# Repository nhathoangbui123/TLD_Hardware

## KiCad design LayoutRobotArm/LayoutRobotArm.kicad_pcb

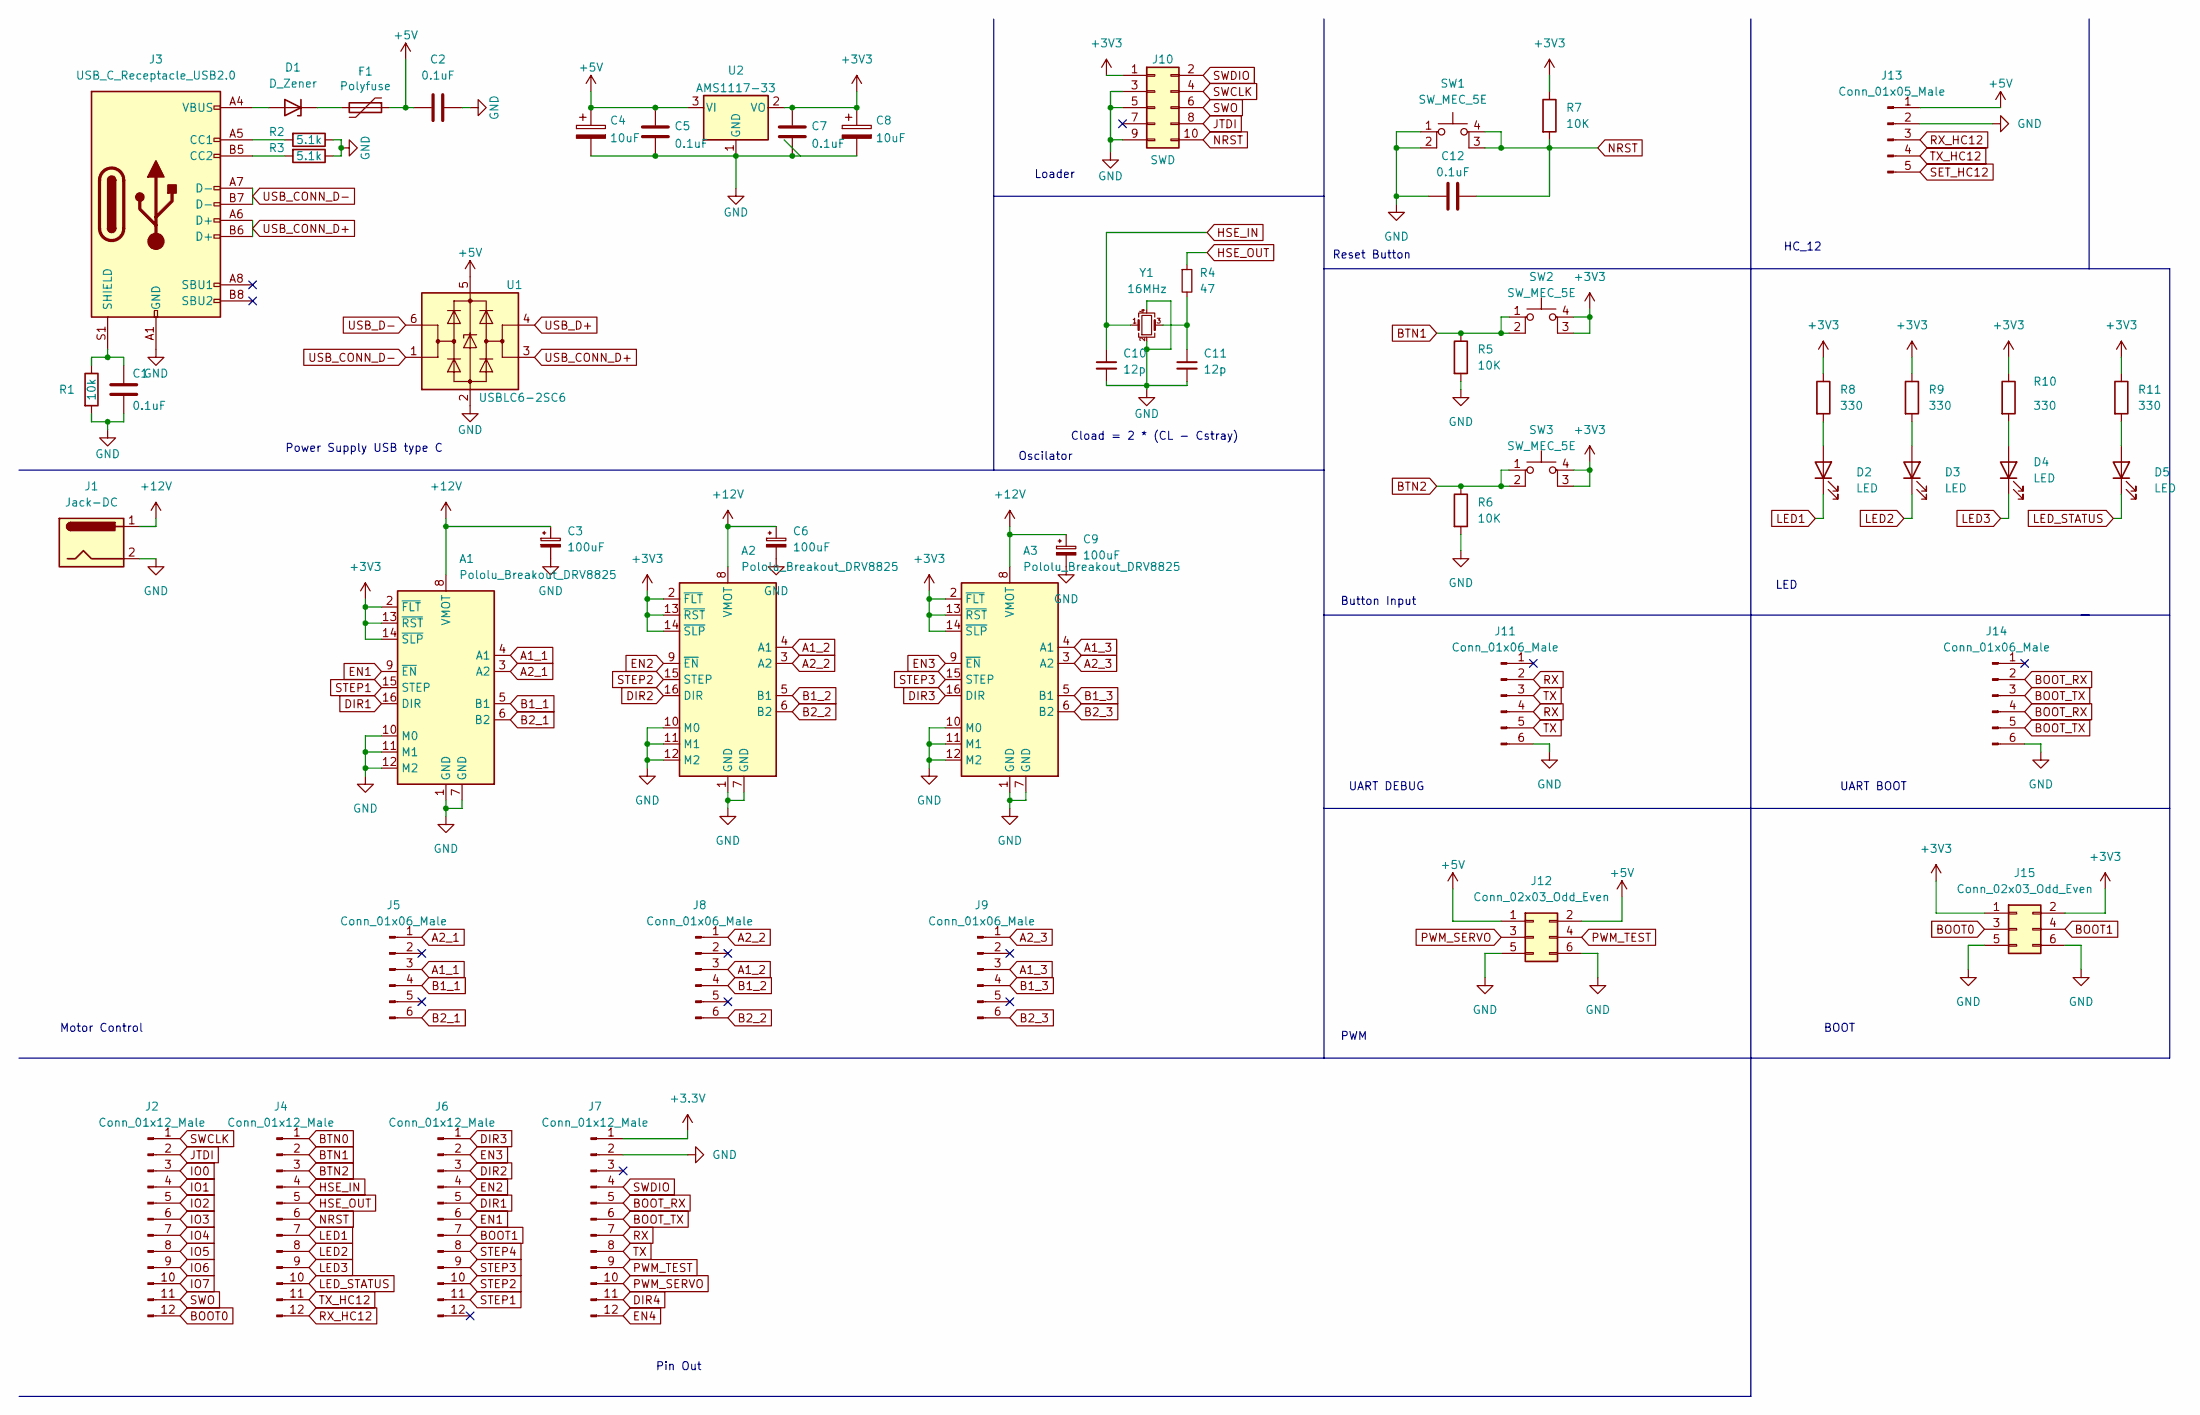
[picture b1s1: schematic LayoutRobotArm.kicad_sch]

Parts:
A1, A2, A3: Pololu_Breakout_DRV8825; Pololu_Breakout-16_15.2x20.3mm
C1, C2, C5, C7, C12: 0.1uF; C_0805_2012Metric
C3, C6, C9: 100uF; CP_Radial_D5.0mm_P2.00mm
C4, C8: 10uF; CP_EIA-3528-12_Kemet-T
C10, C11: 12p; C_0805_2012Metric; LCSC Part # C1547
D1: D_Zener; D_0805_2012Metric
D2, D3, D4, D5: LED; LED_0805_2012Metric
F1: Polyfuse; Fuse_1206
J1: Jack-DC; BarrelJack_Horizontal
J2, J4, J6, J7: Conn_01x12_Male; PinHeader_1x12_P2.54mm_Vertical
J3: USB_C_Receptacle_USB2.0; USB_C_Receptacle_HRO_TYPE-C-31-M-12
J5, J8, J9: Conn_01x06_Male; PinHeader_1x06_P2.00mm_Vertical
J10: SWD; PinHeader_2x05_P2.54mm_Vertical
J11, J14: Conn_01x06_Male; PinHeader_1x06_P2.54mm_Vertical
J12, J15: Conn_02x03_Odd_Even; PinHeader_2x03_P2.54mm_Vertical
J13: Conn_01x05_Male; PinHeader_1x05_P2.54mm_Vertical
R1: 10k; R_0805_2012Metric
R2, R3: 5.1k; R_0805_2012Metric
R4: 47; R_0805_2012Metric; LCSC Part # C25118
R5, R6, R7: 10K; R_0805_2012Metric
R8, R9, R10, R11: 330; R_0805_2012Metric
SW1, SW2, SW3: SW_MEC_5E; SW_Push_1P1T_NO_6x6mm_H9.5mm
U1: USBLC6-2SC6; SOT-23-6; LCSC Part # C7519
U2: AMS1117-33; SOT-223
Y1: 16MHz; Crystal_SMD_3225-4Pin_3.2x2.5mm; LCSC Part # C13738

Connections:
+5V: C2.1, C4.1, C5.1, F1.1, J12.1, J12.2, J13.1, U1.5 (VBUS), U2.3 (VI)
+12V: A1.8 (VMOT), A2.8 (VMOT), A3.8 (VMOT), C3.1, C6.1, C9.1, J1.1
A1_1: A1.4 (A1), J5.3
A1_2: A2.4 (A1), J8.3
A1_3: A3.4 (A1), J9.3
A2_1: A1.3 (A2), J5.1
A2_2: A2.3 (A2), J8.1
A2_3: A3.3 (A2), J9.1
B1_1: A1.5 (B1), J5.4
B1_2: A2.5 (B1), J8.4
B1_3: A3.5 (B1), J9.4
B2_1: A1.6 (B2), J5.6
B2_2: A2.6 (B2), J8.6
B2_3: A3.6 (B2), J9.6
BOOT0: J2.12, J15.3
BOOT1: J6.7, J15.4
BOOT_RX: J7.5, J14.2, J14.4
BOOT_TX: J7.6, J14.3, J14.5
BTN0: J4.1
BTN1: J4.2, R5.1, SW2.1, SW2.2
BTN2: J4.3, R6.1, SW3.1, SW3.2
DIR1: A1.16 (DIR), J6.5
DIR2: A2.16 (DIR), J6.3
DIR3: A3.16 (DIR), J6.1
DIR4: J7.11
EN1: A1.9 (~EN), J6.6
EN2: A2.9 (~EN), J6.4
EN3: A3.9 (~EN), J6.2
EN4: J7.12
GND: A1.1 (GND), A1.7 (GND), A1.10 (M0), A1.11 (M1), A1.12 (M2), A2.1 (GND), A2.7 (GND), A2.10 (M0), A2.11 (M1), A2.12 (M2), A3.1 (GND), A3.7 (GND), A3.10 (M0), A3.11 (M1), A3.12 (M2), C1.1, C2.2, C3.2, C4.2, C5.2, C6.2, C7.2, C8.2, C9.2, C10.2, C11.2, C12.1, J1.2, J3.A1 (GND), J3.A12 (GND), J3.B1 (GND), J3.B12 (GND), J7.2, J10.3, J10.5, J10.9, J11.6, J12.5, J12.6, J13.2, J14.6, J15.5, J15.6, R1.2, R2.1, R3.1, R5.2, R6.2, SW1.1, SW1.2, U1.2 (GND), U2.1 (GND), Y1.2, Y1.4
HSE_IN: C10.1, J4.4, Y1.1
HSE_OUT: J4.5, R4.1
IO0: J2.3
IO1: J2.4
IO2: J2.5
IO3: J2.6
IO4: J2.7
IO5: J2.8
IO6: J2.9
IO7: J2.10
JTDI: J2.2, J10.8
LED1: D2.1 (K), J4.7
LED2: D3.1 (K), J4.8
LED3: D4.1 (K), J4.9
LED_STATUS: D5.1 (K), J4.10
NRST: C12.2, J4.6, J10.10, R7.2, SW1.3 (K), SW1.4 (A)
unnamed: C1.2, J3.S1 (SHIELD), R1.1
unnamed: C11.1, R4.2, Y1.3
unnamed: D1.1 (K), F1.2
unnamed: D1.2 (A), J3.A4 (VBUS), J3.A9 (VBUS), J3.B4 (VBUS), J3.B9 (VBUS)
unnamed: D2.2 (A), R8.2
unnamed: D3.2 (A), R9.2
unnamed: D4.2 (A), R10.2
unnamed: D5.2 (A), R11.2
unnamed: J3.A5 (CC1), R2.2
unnamed: J3.B5 (CC2), R3.2
PWM_SERVO: J7.10, J12.3
PWM_TEST: J7.9, J12.4
RX: J7.7, J11.2, J11.4
RX_HC12: J4.12, J13.3
SET_HC12: J13.5
STEP1: A1.15 (STEP), J6.11
STEP2: A2.15 (STEP), J6.10
STEP3: A3.15 (STEP), J6.9
STEP4: J6.8
SWCLK: J2.1, J10.4
SWDIO: J7.4, J10.2
SWO: J2.11, J10.6
TX: J7.8, J11.3, J11.5
TX_HC12: J4.11, J13.4
USB_CONN_D+: J3.A6 (D+), J3.B6 (D+), U1.3 (I/O2)
USB_CONN_D-: J3.A7 (D-), J3.B7 (D-), U1.1 (I/O1)
USB_D+: U1.4 (I/O2)
USB_D-: U1.6 (I/O1)

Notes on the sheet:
Pin Out
LED
Loader
Cload = 2 * (CL - Cstray)
Button Input
Power Supply USB type C
Reset Button
PWM
Oscilator
BOOT
Motor Control
UART DEBUG
HC_12
UART BOOT

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
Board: 2 copper layers, 52 parts (0 on the bottom side), 59 nets, no tracks yet.

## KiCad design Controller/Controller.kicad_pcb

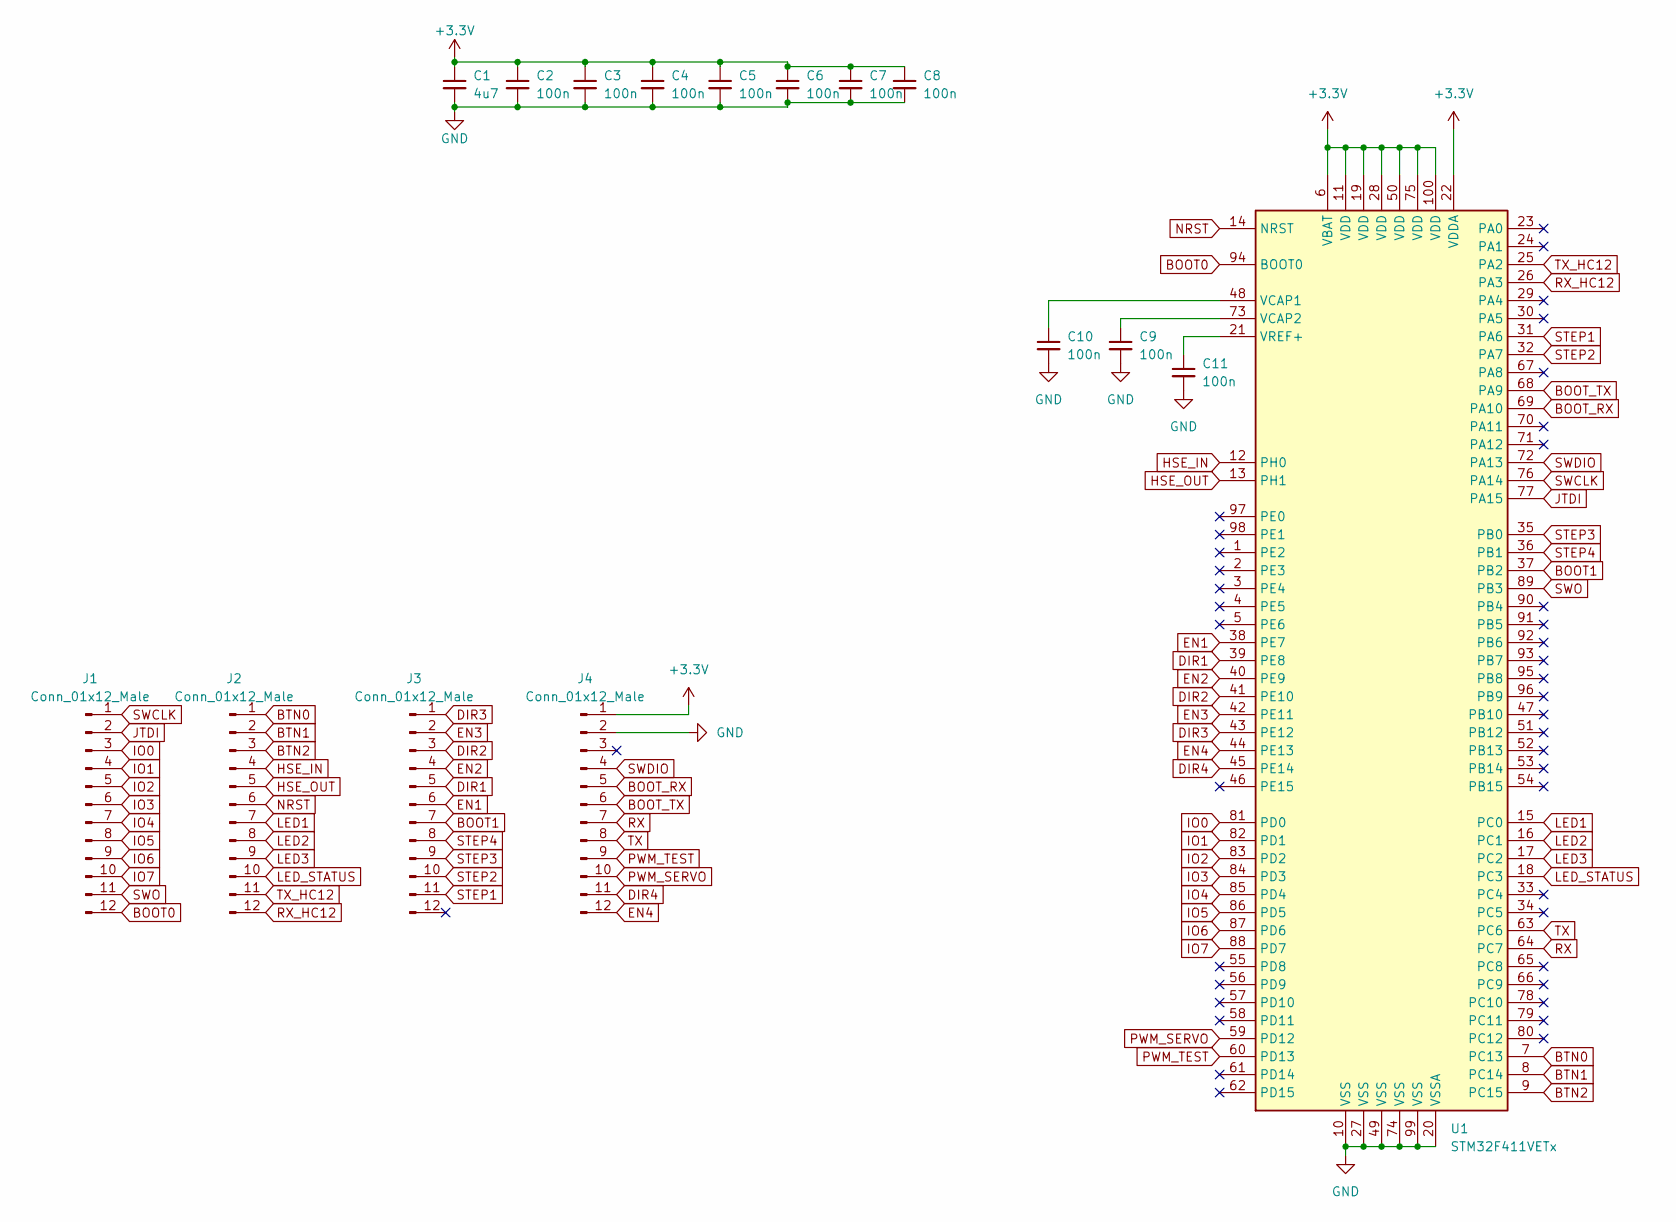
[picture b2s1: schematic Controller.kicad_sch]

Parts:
C1: 4u7; C_0603_1608Metric; LCSC Part # C19666
C2, C3, C4, C5, C6, C7, C8, C9, C10, C11: 100n; C_0402_1005Metric; LCSC Part # C1525
J1, J2, J3, J4: Conn_01x12_Male; PinHeader_1x12_P2.54mm_Vertical
U1: STM32F411VETx; LQFP-100_14x14mm_P0.5mm

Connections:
+3V3: C1.1, C2.1, C3.1, C4.1, C5.1, C6.1, C7.1, C8.1, J4.1, U1.6 (VBAT), U1.11 (VDD), U1.19 (VDD), U1.22 (VDDA), U1.28 (VDD), U1.50 (VDD), U1.75 (VDD), U1.100 (VDD)
BOOT0: J1.12, U1.94 (BOOT0)
BOOT1: J3.7, U1.37 (PB2)
BOOT_RX: J4.5, U1.69 (PA10)
BOOT_TX: J4.6, U1.68 (PA9)
BTN0: J2.1, U1.7 (PC13)
BTN1: J2.2, U1.8 (PC14)
BTN2: J2.3, U1.9 (PC15)
DIR1: J3.5, U1.39 (PE8)
DIR2: J3.3, U1.41 (PE10)
DIR3: J3.1, U1.43 (PE12)
DIR4: J4.11, U1.45 (PE14)
EN1: J3.6, U1.38 (PE7)
EN2: J3.4, U1.40 (PE9)
EN3: J3.2, U1.42 (PE11)
EN4: J4.12, U1.44 (PE13)
GND: C1.2, C2.2, C3.2, C4.2, C5.2, C6.2, C7.2, C8.2, C9.2, C10.2, C11.2, J4.2, U1.10 (VSS), U1.20 (VSSA), U1.27 (VSS), U1.49 (VSS), U1.74 (VSS), U1.99 (VSS)
HSE_IN: J2.4, U1.12 (PH0)
HSE_OUT: J2.5, U1.13 (PH1)
IO0: J1.3, U1.81 (PD0)
IO1: J1.4, U1.82 (PD1)
IO2: J1.5, U1.83 (PD2)
IO3: J1.6, U1.84 (PD3)
IO4: J1.7, U1.85 (PD4)
IO5: J1.8, U1.86 (PD5)
IO6: J1.9, U1.87 (PD6)
IO7: J1.10, U1.88 (PD7)
JTDI: J1.2, U1.77 (PA15)
LED1: J2.7, U1.15 (PC0)
LED2: J2.8, U1.16 (PC1)
LED3: J2.9, U1.17 (PC2)
LED_STATUS: J2.10, U1.18 (PC3)
NRST: J2.6, U1.14 (NRST)
unnamed: C9.1, U1.73 (VCAP2)
unnamed: C10.1, U1.48 (VCAP1)
unnamed: C11.1, U1.21 (VREF+)
PWM_SERVO: J4.10, U1.59 (PD12)
PWM_TEST: J4.9, U1.60 (PD13)
RX: J4.7, U1.64 (PC7)
RX_HC12: J2.12, U1.26 (PA3)
STEP1: J3.11, U1.31 (PA6)
STEP2: J3.10, U1.32 (PA7)
STEP3: J3.9, U1.35 (PB0)
STEP4: J3.8, U1.36 (PB1)
SWCLK: J1.1, U1.76 (PA14)
SWDIO: J4.4, U1.72 (PA13)
SWO: J1.11, U1.89 (PB3)
TX: J4.8, U1.63 (PC6)
TX_HC12: J2.11, U1.25 (PA2)

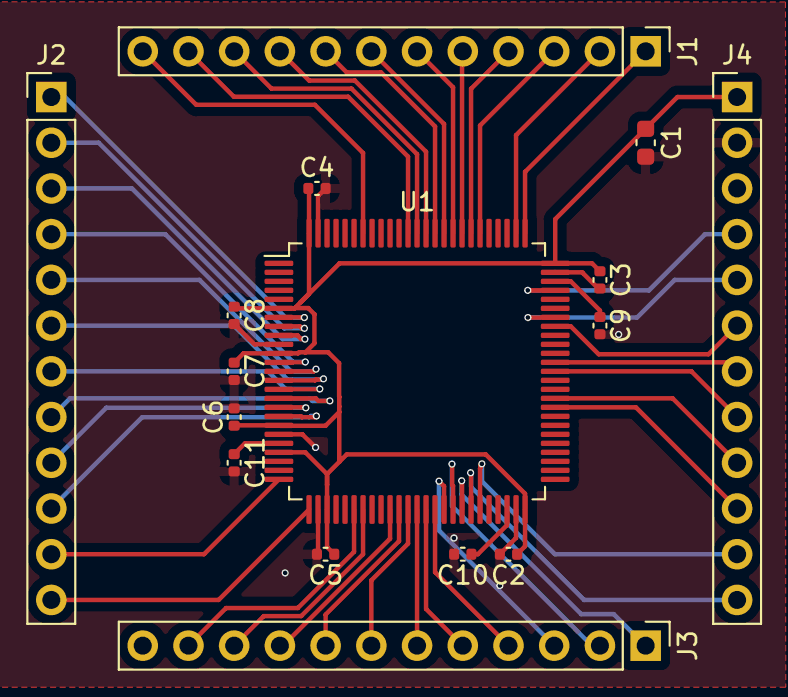
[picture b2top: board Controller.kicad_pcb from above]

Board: 2 copper layers, 16 parts (0 on the bottom side), 49 nets.

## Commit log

2022-06-07 Update layout
